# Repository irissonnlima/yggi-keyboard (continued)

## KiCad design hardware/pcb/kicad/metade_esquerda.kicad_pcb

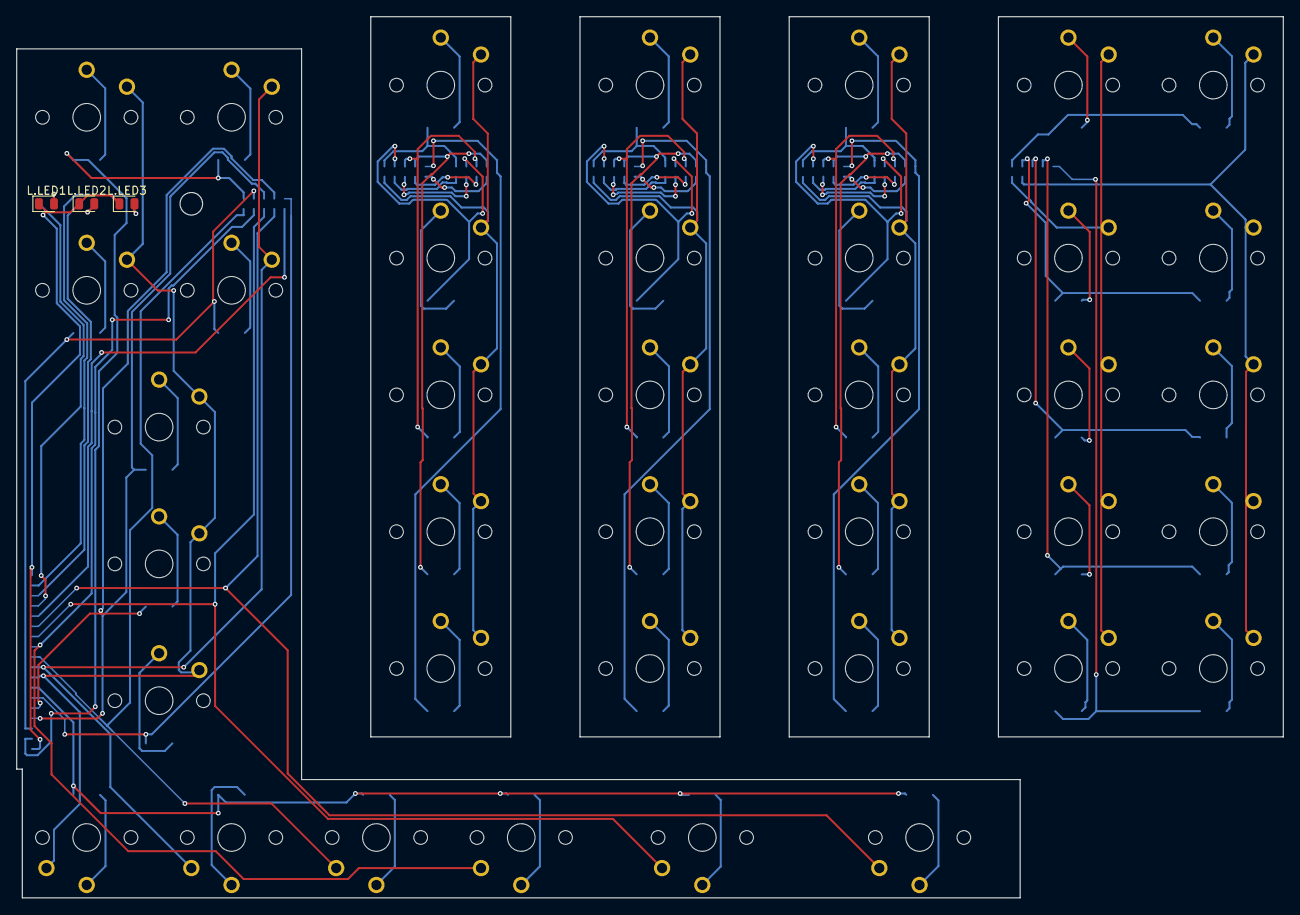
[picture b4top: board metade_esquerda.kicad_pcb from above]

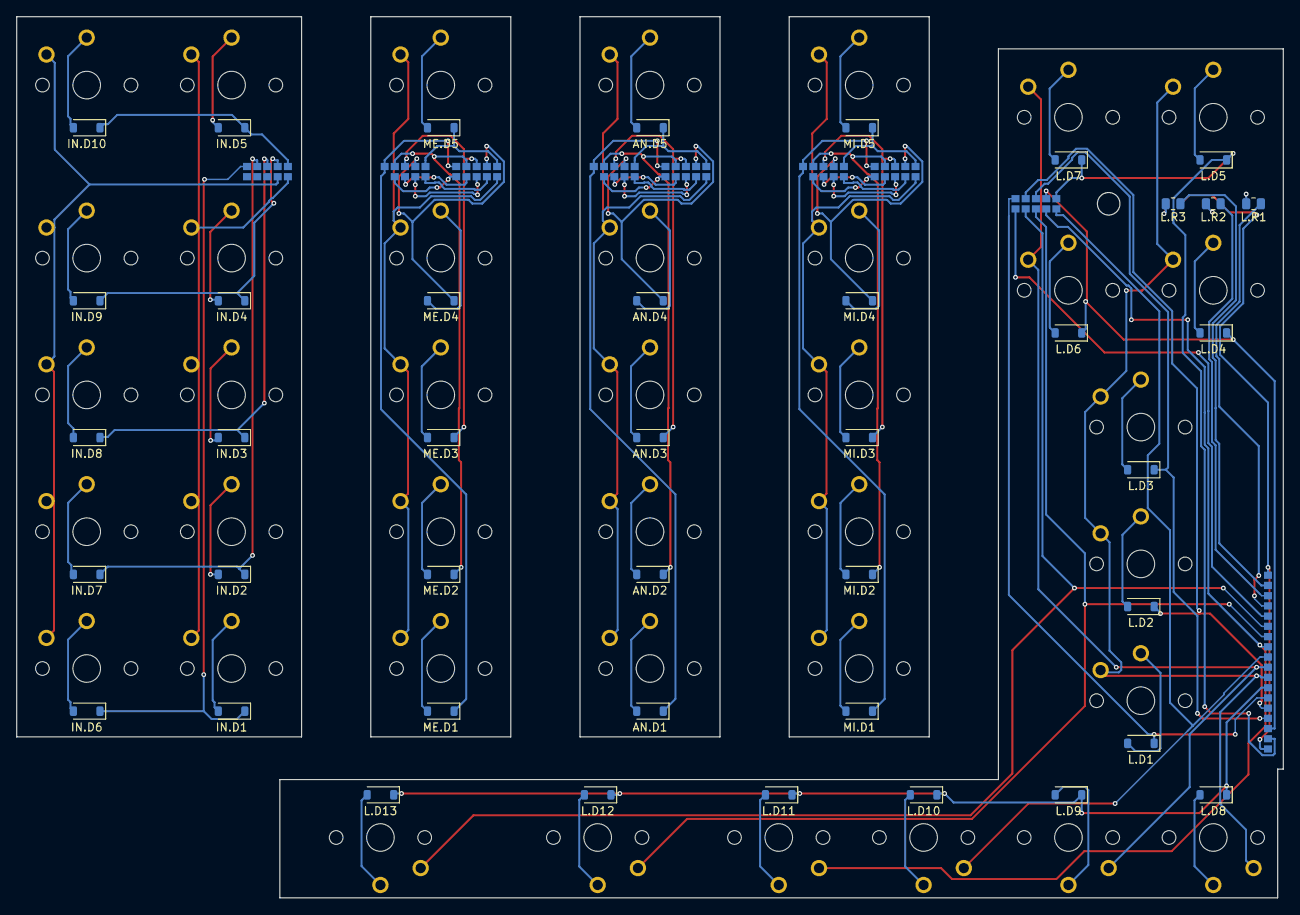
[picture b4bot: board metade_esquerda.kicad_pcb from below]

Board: 2 copper layers, 157.4 x 109.5 mm, 177 parts (41 on the bottom side), 61 nets.

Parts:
AN.D1, AN.D2, AN.D3, AN.D4, AN.D5: 1N4148W; D_SOD-123
AN.PAD1, AN.PAD2, AN.PAD3, AN.PAD4, AN.PAD5, AN.PAD6, AN.PAD7, AN.PAD8, AN.PAD9, AN.PAD10, AN.PAD11, AN.PAD12, AN.PAD13, AN.PAD14, AN.PAD15, AN.PAD16, AN.PAD17, AN.PAD18, AN.PAD19: SMDPad
AN.S1, AN.S2, AN.S3, AN.S4, AN.S5: PG1350
IN.D1, IN.D2, IN.D3, IN.D4, IN.D5, IN.D6, IN.D7, IN.D8, IN.D9, IN.D10: 1N4148W; D_SOD-123
IN.PAD1, IN.PAD2, IN.PAD3, IN.PAD4, IN.PAD5, IN.PAD6, IN.PAD7, IN.PAD8, IN.PAD9, IN.PAD10: SMDPad
IN.S1, IN.S2, IN.S3, IN.S4, IN.S5, IN.S6, IN.S7, IN.S8, IN.S9, IN.S10: PG1350
L.D1, L.D2, L.D3, L.D4, L.D5, L.D6, L.D7, L.D8, L.D9, L.D10, L.D11, L.D12, L.D13: 1N4148W; D_SOD-123
L.LED1, L.LED2, L.LED3: LED 0805; LED_0805_2012Metric
L.PAD1, L.PAD2, L.PAD3, L.PAD4, L.PAD5, L.PAD6, L.PAD7, L.PAD8, L.PAD9, L.PAD10, L.PAD11, L.PAD12, L.PAD13, L.PAD14, L.PAD15, L.PAD16, L.PAD17, L.PAD18, L.PAD19, L.PAD20, L.PAD21, L.PAD22, L.PAD23, L.PAD24, L.PAD25, L.PAD26, L.PAD27, L.PAD28: SMDPad
L.R1, L.R2, L.R3: 1k; R_0805_2012Metric
L.S1, L.S2, L.S3, L.S4, L.S5, L.S6, L.S7, L.S8, L.S9, L.S10, L.S11, L.S12, L.S13: PG1350
ME.D1, ME.D2, ME.D3, ME.D4, ME.D5: 1N4148W; D_SOD-123
ME.PAD1, ME.PAD2, ME.PAD3, ME.PAD4, ME.PAD5, ME.PAD6, ME.PAD7, ME.PAD8, ME.PAD9, ME.PAD10, ME.PAD11, ME.PAD12, ME.PAD13, ME.PAD14, ME.PAD15, ME.PAD16, ME.PAD17, ME.PAD18, ME.PAD19: SMDPad
ME.S1, ME.S2, ME.S3, ME.S4, ME.S5: PG1350
MI.D1, MI.D2, MI.D3, MI.D4, MI.D5: 1N4148W; D_SOD-123
MI.PAD1, MI.PAD2, MI.PAD3, MI.PAD4, MI.PAD5, MI.PAD6, MI.PAD7, MI.PAD8, MI.PAD9, MI.PAD10, MI.PAD11, MI.PAD12, MI.PAD13, MI.PAD14, MI.PAD15, MI.PAD16, MI.PAD17, MI.PAD18, MI.PAD19: SMDPad
MI.S1, MI.S2, MI.S3, MI.S4, MI.S5: PG1350

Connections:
AN.c1_r0: AN.D5.2, AN.S5.2
AN.c1_r1: AN.D4.2, AN.S4.2
AN.c1_r2: AN.D3.2, AN.S3.2
AN.c1_r3: AN.D2.2, AN.S2.2
AN.c1_r4: AN.D1.2, AN.S1.2
AN.livre.C5: AN.PAD10.1, AN.PAD19.1
COL0: L.PAD18.1, L.S1.1, L.S2.1, L.S3.1, L.S4.1, L.S5.1, L.S8.1
COL1: L.PAD19.1, L.S6.1, L.S7.1, L.S9.1
COL2: L.PAD6.1, L.PAD20.1, L.S10.1, MI.PAD6.1, MI.S1.1, MI.S2.1, MI.S3.1, MI.S4.1, MI.S5.1
COL3: AN.PAD6.1, AN.S1.1, AN.S2.1, AN.S3.1, AN.S4.1, AN.S5.1, L.PAD7.1, L.PAD21.1, L.S11.1, MI.PAD7.1, MI.PAD16.1
COL4: AN.PAD7.1, AN.PAD16.1, L.PAD8.1, L.PAD22.1, L.S12.1, ME.PAD6.1, ME.S1.1, ME.S2.1, ME.S3.1, ME.S4.1, ME.S5.1, MI.PAD8.1, MI.PAD17.1
COL5: AN.PAD8.1, AN.PAD17.1, IN.PAD6.1, IN.S1.1, IN.S2.1, IN.S3.1, IN.S4.1, IN.S5.1, L.PAD9.1, L.PAD23.1, L.S13.1, ME.PAD7.1, ME.PAD16.1, MI.PAD9.1, MI.PAD18.1
COL6: AN.PAD9.1, AN.PAD18.1, IN.PAD7.1, IN.S6.1, IN.S7.1, IN.S8.1, IN.S9.1, IN.S10.1, L.PAD10.1, L.PAD24.1, ME.PAD8.1, ME.PAD17.1, MI.PAD10.1, MI.PAD19.1
GND: L.LED1.1, L.LED2.1, L.LED3.1, L.PAD11.1, L.PAD28.1
IN.c1_r0: IN.D5.2, IN.S5.2
IN.c1_r1: IN.D4.2, IN.S4.2
IN.c1_r2: IN.D3.2, IN.S3.2
IN.c1_r3: IN.D2.2, IN.S2.2
IN.c1_r4: IN.D1.2, IN.S1.2
IN.c2_r0: IN.D10.2, IN.S10.2
IN.c2_r1: IN.D9.2, IN.S9.2
IN.c2_r2: IN.D8.2, IN.S8.2
IN.c2_r3: IN.D7.2, IN.S7.2
IN.c2_r4: IN.D6.2, IN.S6.2
L.c0_r0: L.D5.2, L.S5.2
L.c0_r1: L.D4.2, L.S4.2
L.c0_r2: L.D3.2, L.S3.2
L.c0_r3: L.D2.2, L.S2.2
L.c0_r4: L.D1.2, L.S1.2
L.c1_r0: L.D7.2, L.S7.2
L.c1_r1: L.D6.2, L.S6.2
L.cmd_r5: L.D11.2, L.S11.2
L.ctl_r5: L.D9.2, L.S9.2
L.del_r5: L.D12.2, L.S12.2
L.fn_r5: L.D8.2, L.S8.2
L.led1_a: L.LED1.2, L.R1.2
L.led2_a: L.LED2.2, L.R2.2
L.led3_a: L.LED3.2, L.R3.2
L.opt_r5: L.D10.2, L.S10.2
L.spc_r5: L.D13.2, L.S13.2
LED1: L.PAD25.1, L.R1.1
LED2: L.PAD26.1, L.R2.1
LED3: L.PAD27.1, L.R3.1
ME.c1_r0: ME.D5.2, ME.S5.2
ME.c1_r1: ME.D4.2, ME.S4.2
ME.c1_r2: ME.D3.2, ME.S3.2
ME.c1_r3: ME.D2.2, ME.S2.2
ME.c1_r4: ME.D1.2, ME.S1.2
ME.livre.C4: ME.PAD9.1, ME.PAD18.1
ME.livre.C5: ME.PAD10.1, ME.PAD19.1
MI.c1_r0: MI.D5.2, MI.S5.2
MI.c1_r1: MI.D4.2, MI.S4.2
MI.c1_r2: MI.D3.2, MI.S3.2
MI.c1_r3: MI.D2.2, MI.S2.2
MI.c1_r4: MI.D1.2, MI.S1.2
R0: AN.D5.1, AN.PAD1.1, AN.PAD11.1, IN.D5.1, IN.D10.1, IN.PAD1.1, L.D5.1, L.D7.1, L.PAD1.1, L.PAD12.1, ME.D5.1, ME.PAD1.1, ME.PAD11.1, MI.D5.1, MI.PAD1.1, MI.PAD11.1
R1: AN.D4.1, AN.PAD2.1, AN.PAD12.1, IN.D4.1, IN.D9.1, IN.PAD2.1, L.D4.1, L.D6.1, L.PAD2.1, L.PAD13.1, ME.D4.1, ME.PAD2.1, ME.PAD12.1, MI.D4.1, MI.PAD2.1, MI.PAD12.1
R2: AN.D3.1, AN.PAD3.1, AN.PAD13.1, IN.D3.1, IN.D8.1, IN.PAD3.1, L.D3.1, L.PAD3.1, L.PAD14.1, ME.D3.1, ME.PAD3.1, ME.PAD13.1, MI.D3.1, MI.PAD3.1, MI.PAD13.1
R3: AN.D2.1, AN.PAD4.1, AN.PAD14.1, IN.D2.1, IN.D7.1, IN.PAD4.1, L.D2.1, L.PAD4.1, L.PAD15.1, ME.D2.1, ME.PAD4.1, ME.PAD14.1, MI.D2.1, MI.PAD4.1, MI.PAD14.1
R4: AN.D1.1, AN.PAD5.1, AN.PAD15.1, IN.D1.1, IN.D6.1, IN.PAD5.1, L.D1.1, L.PAD5.1, L.PAD16.1, ME.D1.1, ME.PAD5.1, ME.PAD15.1, MI.D1.1, MI.PAD5.1, MI.PAD15.1
R5: L.D8.1, L.D9.1, L.D10.1, L.D11.1, L.D12.1, L.D13.1, L.PAD17.1
